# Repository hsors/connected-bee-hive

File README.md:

# ardbeescale-for-dummies

This repo includes the code of a a connected bee hive project together with a 65 pages document explaining the project in all details, including hardware and software 

My implementation is classical (Arduino/LoRaWan/NodeRED/InfluxDB/Grafana) but I also have included a Google Sheet integration retrieving the hive data in a google sheet, which is convenient for calibration purposes. The data being transmitted are weight, external temperature, humidity and pressure plus internal brood temperature. The data are transmitted every 15mn by default but this is configurable by sending an ad hoc downlink to the hive (a python script is provided to send downlinks to the hives). 

My code includes a weight temperature compensation algorithm using a nonlinear model which has proven to be effective and which is described precisely in the document. 

My connected bee hives include a small sirup pump allowing to feed the hives remotely. This is both convenient when the apiary is not close by and very effective to develop the hives in the spring or before winter (feeding with a small quantity of sugar very often seems to be more effective than a bigger quantity less often). The application includes a smartphone app from which the user can trigger the pumps (the app is communicating with a set of python scripts which send some uplink information to the app and get input from the app to send downlinks to the hives). From the same app, it’s possible to send a downlink which prevent the hive from sending data during a certain pre-determined time (when hives are open, we want to avoid to plot a wrong point on the hive weight curve). 

My apiary being too far away from the closest LoRaWAN gateway I had to add one (with the 4G option), which is powered from a 12V battery charged with PV panels. The gateway being quite power angry, it is switched on by an “energy saving device” only when uploads are transmitted by the scales. My code includes therefore a mechanism which synchronizes the time of each scale and the one of the energy saver device with TTN time. The  time synchronization logic is controlled by two python scripts which can be launched either manually or at regular time intervals such as once a week, to set the time of the nodes: the first script is listening to the next uplink sent by a node. The second one is triggered when this next uplink is received, at which time it sends a “set time” downlink to the node with the time of this last received uplink to which the duration between two measures is added.

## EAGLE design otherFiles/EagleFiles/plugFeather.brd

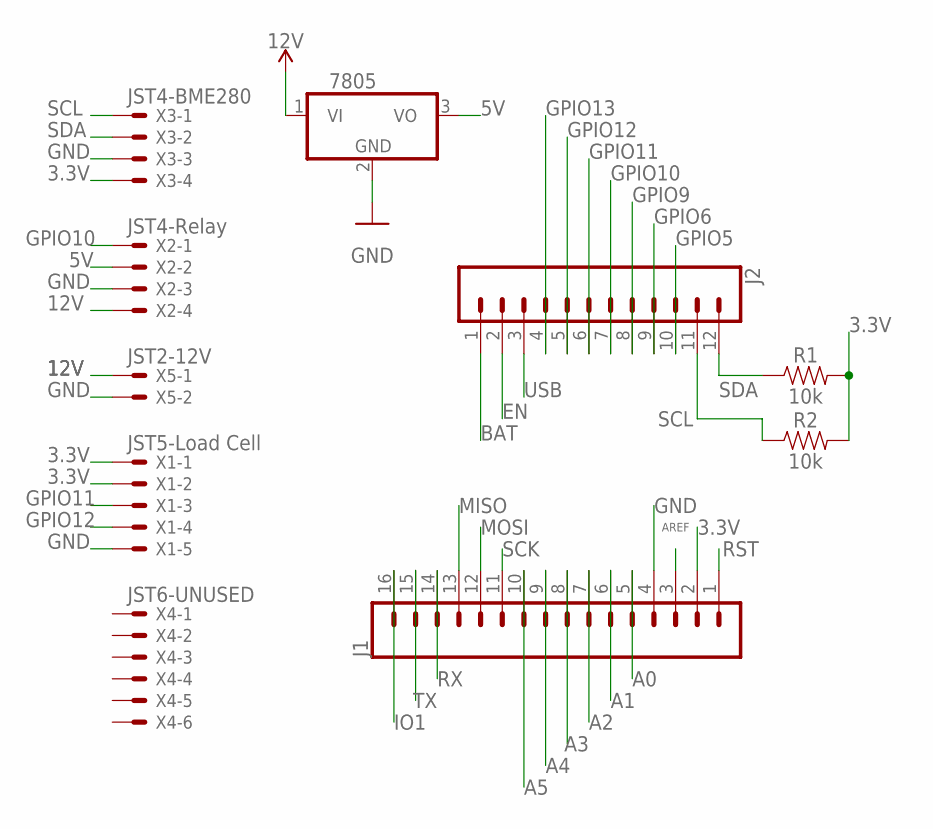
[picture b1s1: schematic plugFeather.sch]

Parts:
IC1: 7805; TO220V
J1: CONN_16; 1X16
J2: CONN_12; 1X12
R1, R2: 10k; AXIAL-0.3
X1: JST5-Load Cell; JST-XH-05-PACKAGE-LONG-PAD
X2: JST4-Relay; JST-XH-04-PACKAGE-LONG-PAD
X3: JST4-BME280; JST-XH-04-PACKAGE-LONG-PAD
X4: JST6-UNUSED; JST-XH-06-PACKAGE-LONG-PAD
X5: JST2-12V; JST-XH-02-PACKAGE-LONG-PAD

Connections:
3.3V: J1.2, R1.P$2 (2), R2.P$2 (2), X1.1, X1.2, X3.4
5V: IC1.3 (VO), X2.2
12V: IC1.1 (VI), X2.4, X5.1
A0: J1.5
A1: J1.6
A2: J1.7
A3: J1.8
A4: J1.9
A5: J1.10
AREF: J1.3
BAT: J2.1
EN: J2.2
GND: IC1.2 (GND), J1.4, X1.5, X2.3, X3.3, X5.2
GPIO5: J2.10
GPIO6: J2.9
GPIO9: J2.8
GPIO10: J2.7, X2.1
GPIO11: J2.6, X1.3
GPIO12: J2.5, X1.4
GPIO13: J2.4
IO1: J1.16
MISO: J1.13
MOSI: J1.12
RST: J1.1
RX: J1.14
SCK: J1.11
SCL: J2.11, R2.P$1 (1), X3.1
SDA: J2.12, R1.P$1 (1), X3.2
TX: J1.15
USB: J2.3

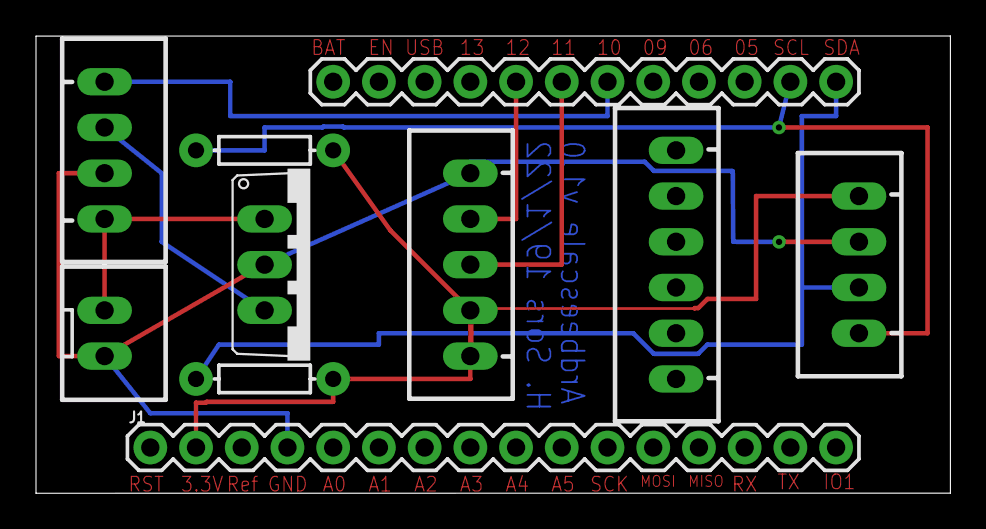
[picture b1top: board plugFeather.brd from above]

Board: 2 copper layers, 50.8 x 25.4 mm, 10 parts (0 on the bottom side), 9 nets.

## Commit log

2023-04-14 Connecte bee hive
    Complete step by step instructions to build a complete connected bee hive including temperature compensated weight, internal and external temp, humidity, pressure. Can also trigger sirup pump.
2023-04-14 Update of the readme file
    Update of the readme file
2023-08-17 add watchdog timer
2023-08-17 add again js file
2023-08-20 Bug correction in the watch dog software
    Bug correction in the watch dog software
2023-10-18 Bug fix
    - Addition of a watchdog routine catching the few cases where the SW hangs because of the BME280 driver failing to correctly read the sensor
    - New version of the instruction file

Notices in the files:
parts and their libraries:
SparkFun-Connectors: Licensing: Creative Commons ShareAlike 4.0 International - https://creativecommons.org/licenses/by-sa/4.0
